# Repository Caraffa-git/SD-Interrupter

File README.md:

# Tesla coil MIDI interrupter
It's modified version of [OneTesla SD interrupter](https://onetesla.com/).
To compile original software you have to install [SdFat v1.1.4](https://github.com/greiman/SdFat/releases/tag/1.1.4) library.

<!--  -->

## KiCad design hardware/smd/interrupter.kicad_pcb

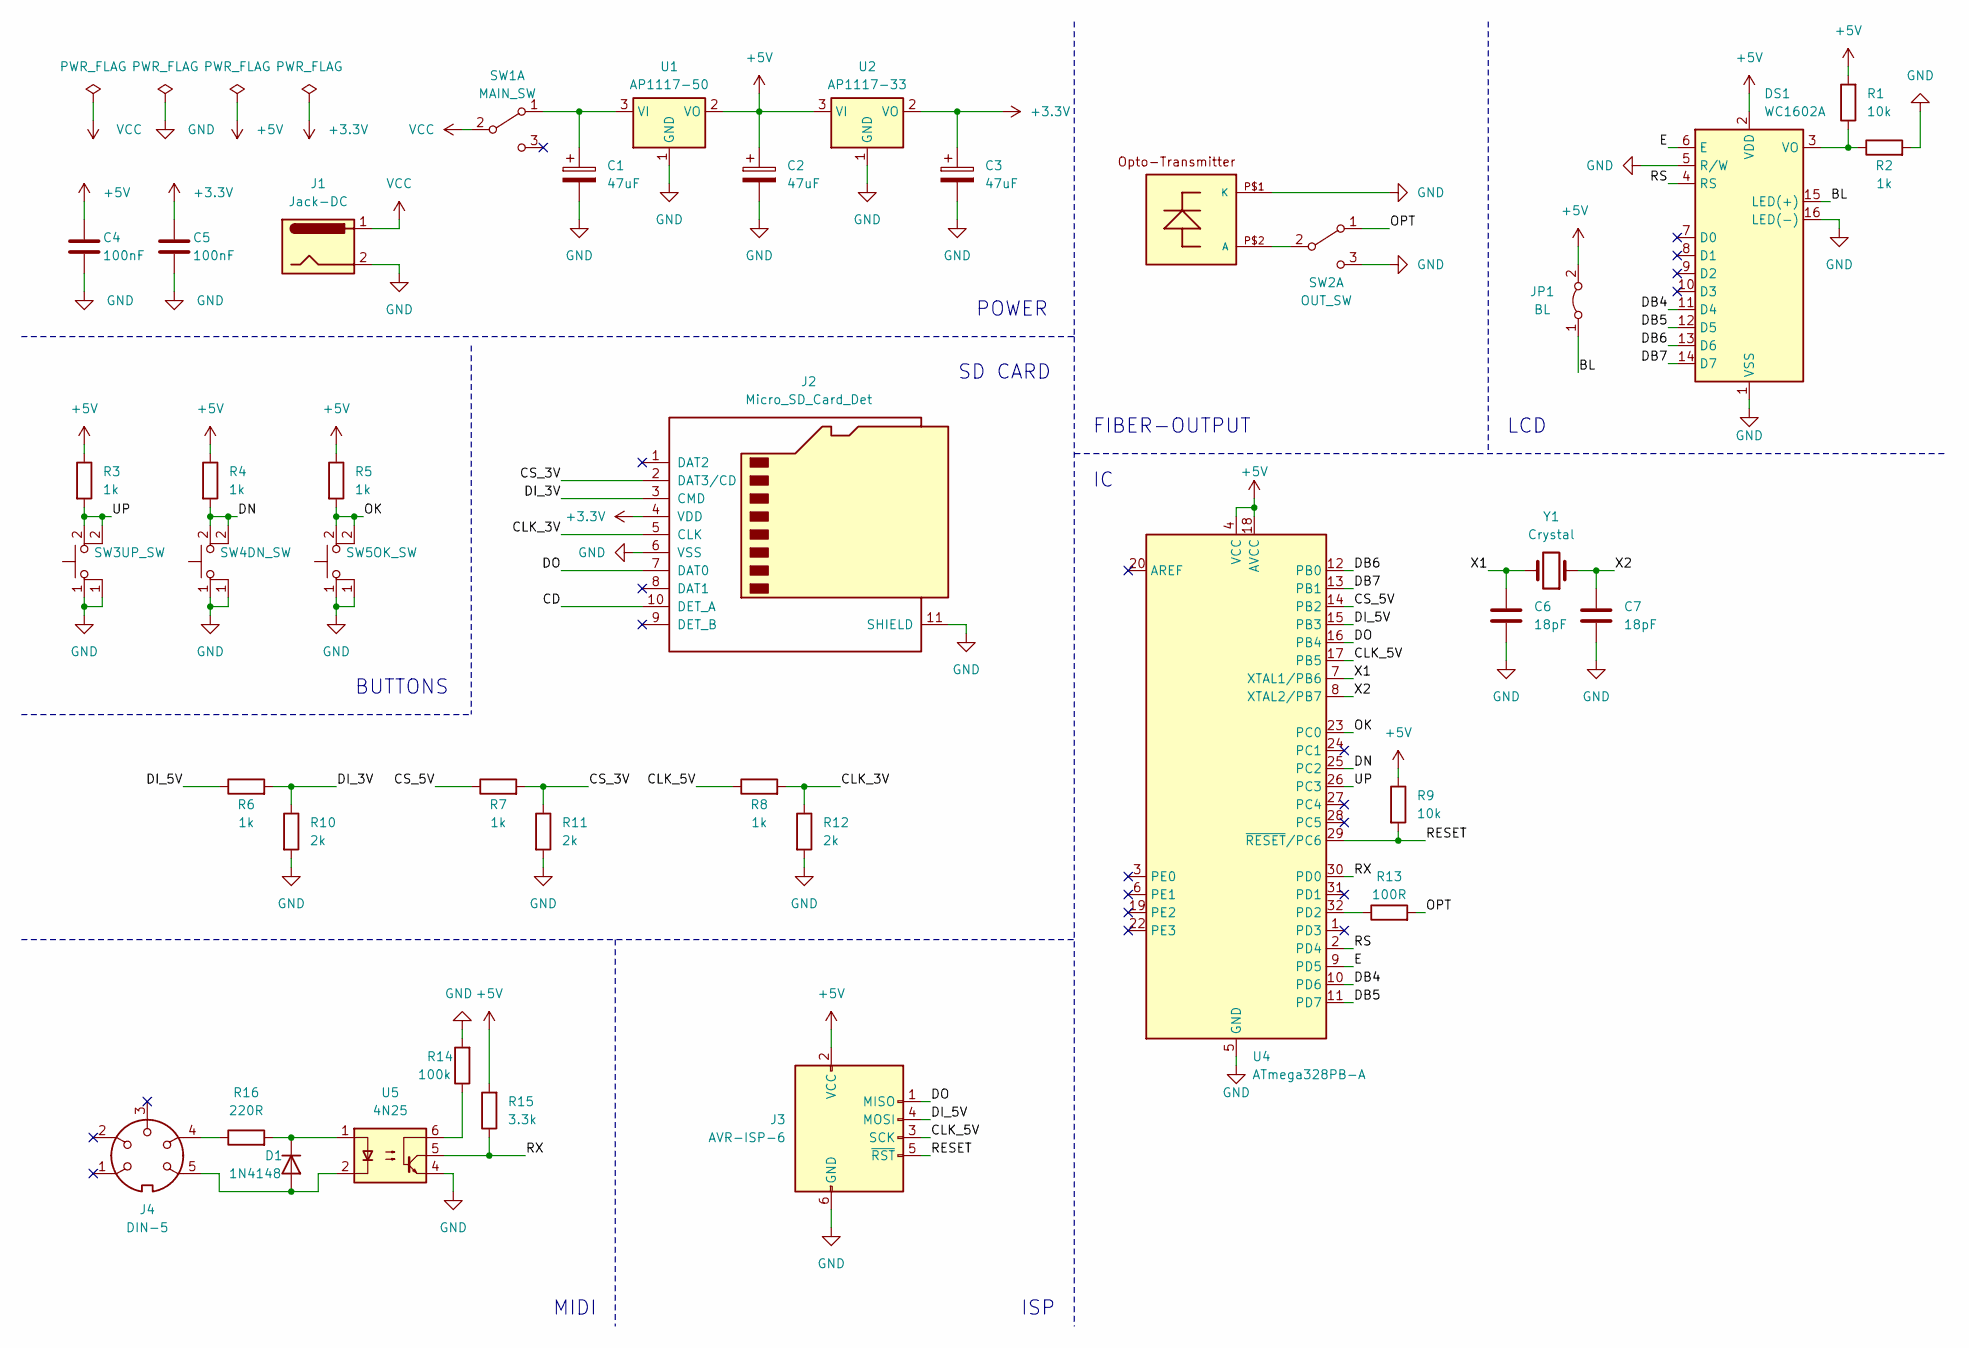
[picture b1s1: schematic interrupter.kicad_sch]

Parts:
C1, C2, C3: 47uF; CP_Radial_D4.0mm_P1.50mm
C4, C5: 100nF; C_0805_2012Metric
C6, C7: 18pF; C_0805_2012Metric
D1: 1N4148; D_SOD-123
DS1: WC1602A
J1: Jack-DC; BarrelJack_Horizontal
J2: Micro_SD_Card_Det; microSD_HC_Hirose_DM3AT-SF-PEJM5
J3: AVR-ISP-6; PinSocket_2x03_P2.54mm_Vertical
J4: DIN-5; din-5
JP1: BL; SolderJumper-2_P1.3mm_Bridged_RoundedPad1.0x1.5mm
R1, R9: 10k; R_0805_2012Metric
R2, R3, R4, R5, R6, R7, R8: 1k; R_0805_2012Metric
R10, R11, R12: 2k; R_0805_2012Metric
R13: 100R; R_0805_2012Metric
R14: 100k; R_0805_2012Metric
R15: 3.3k; R_0805_2012Metric
R16: 220R; R_0805_2012Metric
SW1: MAIN_SW; Switch 12x6mm
SW2: OUT_SW; Switch 12x6mm
SW3: UP_SW; SW_PUSH_6mm_H7.3mm
SW4: DN_SW; SW_PUSH_6mm_H7.3mm
SW5: OK_SW; SW_PUSH_6mm_H7.3mm
U1: AP1117-50; SOT-223-3_TabPin2
U2: AP1117-33; SOT-223-3_TabPin2
U3: IFE91A; OPTO-TRANSMITTER
U4: ATmega328PB-A; TQFP-32_7x7mm_P0.8mm
U5: 4N25; DIP-6_W7.62mm
Y1: Crystal; Crystal_HC49-4H_Vertical

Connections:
+3.3V: C3.1, C5.1, J2.4 (VDD), U2.2 (VO)
+5V: C2.1, C4.1, DS1.2 (VDD), J3.2 (VCC), JP1.2 (B), R1.2, R3.1, R4.1, R5.1, R9.1, R15.2, U1.2 (VO), U2.3 (VI), U4.4 (VCC), U4.18 (AVCC)
/BL: DS1.15 (LED(+)), JP1.1 (A)
/CD: J2.10 (DET_A)
/CLK_3V: J2.5 (CLK), R8.2, R12.1; also elsewhere on the board
/CLK_5V: J3.3 (SCK), R8.1, U4.17 (PB5)
/CS_3V: J2.2 (DAT3/CD), R7.2, R11.1
/CS_5V: R7.1, U4.14 (PB2)
/DB4: DS1.11 (D4), U4.10 (PD6)
/DB5: DS1.12 (D5), U4.11 (PD7)
/DB6: DS1.13 (D6), U4.12 (PB0)
/DB7: DS1.14 (D7), U4.13 (PB1)
/DI_3V: J2.3 (CMD), R6.2, R10.1
/DI_5V: J3.4 (MOSI), R6.1, U4.15 (PB3)
/DN: R4.2, SW4.2 (A), U4.25 (PC2)
/DO: J2.7 (DAT0), J3.1 (MISO), U4.16 (PB4)
/E: DS1.6 (E), U4.9 (PD5)
/OK: R5.2, SW5.2 (A), U4.23 (PC0)
/OPT: R13.2, SW2.1 (A)
/RESET: J3.5 (~RST), R9.2, U4.29 (~RESET/PC6)
/RS: DS1.4 (RS), U4.2 (PD4)
/RX: R15.1, U4.30 (PD0), U5.5
/UP: R3.2, SW3.2 (K), U4.26 (PC3)
/X1: C6.1, U4.7 (XTAL1/PB6), Y1.2
/X2: C7.1, U4.8 (XTAL2/PB7), Y1.1
GND: C1.2, C2.2, C3.2, C4.2, C5.2, C6.2, C7.2, DS1.1 (VSS), DS1.5 (R/W), DS1.16 (LED(-)), J1.2, J2.6 (VSS), J2.11 (SHIELD), J3.6 (GND), R2.2, R10.2, R11.2, R12.2, R14.2, SW2.3 (C), SW3.1, SW4.1, SW5.1, U1.1 (GND), U2.1 (GND), U3.P$1 (K), U4.5 (GND), U4.21 (GND), U5.4; also elsewhere on the board
unnamed: D1.2 (A), J4.5, U5.2
unnamed: D1.1 (K), R16.2, U5.1
unnamed: DS1.3 (VO), R1.1, R2.1
unnamed: J4.4, R16.1
unnamed: R14.1, U5.6
unnamed: C1.1, SW1.1 (A), U1.3 (VI)
unnamed: SW2.2 (B), U3.P$2 (A)
unnamed: R13.1, U4.32 (PD2)
VCC: J1.1, SW1.2 (B)

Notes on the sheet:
ISP
SD CARD
MIDI
POWER
FIBER-OUTPUT
LCD
BUTTONS

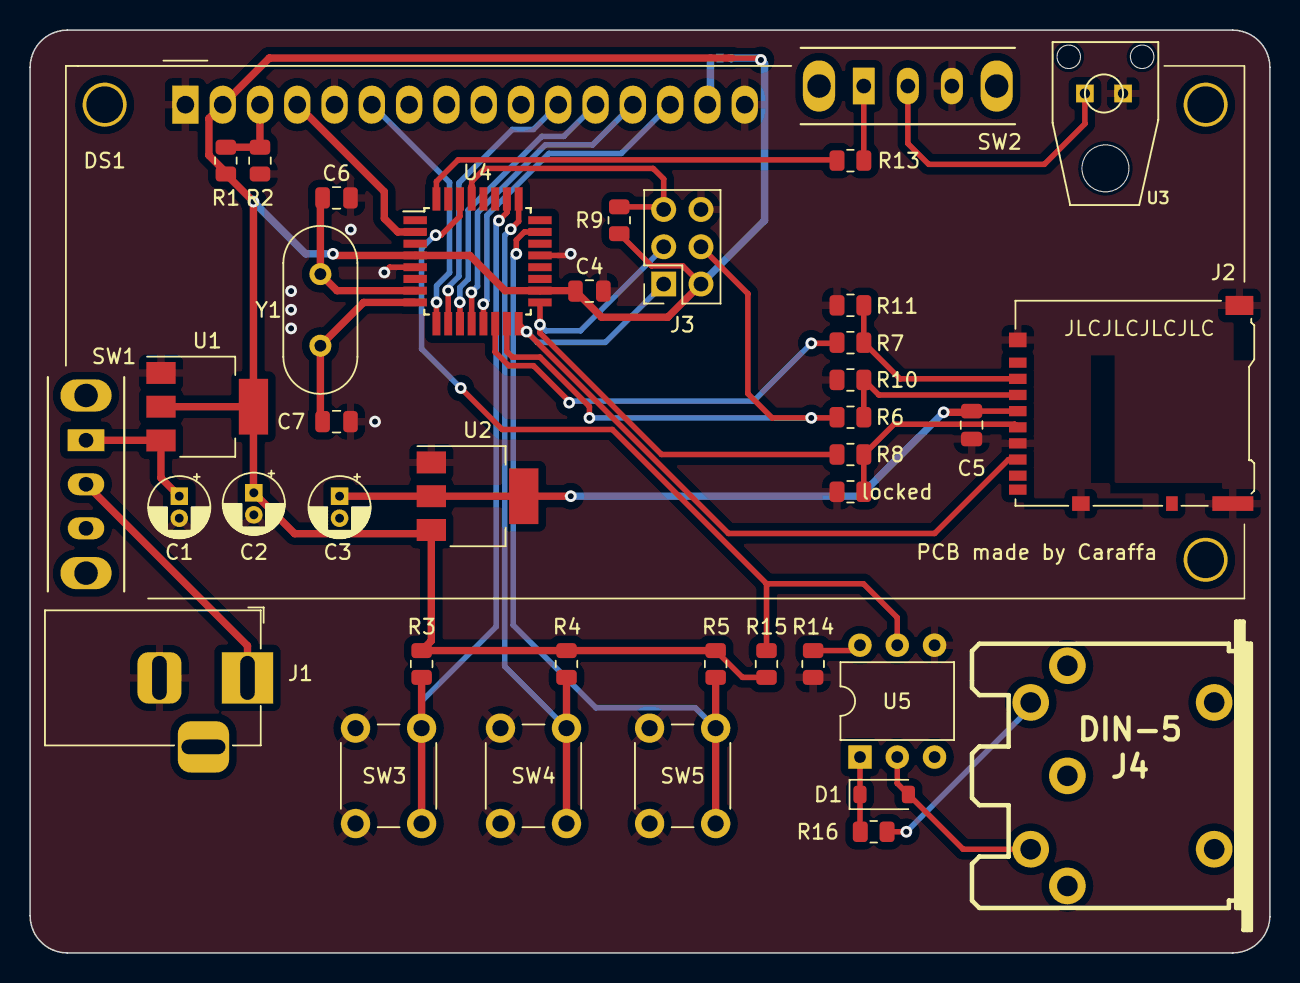
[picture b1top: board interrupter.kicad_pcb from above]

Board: 2 copper layers, 84.5 x 62.9 mm, 41 parts (1 on the bottom side), 34 nets.

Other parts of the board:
locked: 2k; R_0805_2012Metric

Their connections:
/CLK_3V: locked.1; also elsewhere on the board
GND: locked.2; also elsewhere on the board

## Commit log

2023-10-16 via fix
2023-10-16 silkscreen fix
2023-10-16 added images
2024-09-16 cleanup
